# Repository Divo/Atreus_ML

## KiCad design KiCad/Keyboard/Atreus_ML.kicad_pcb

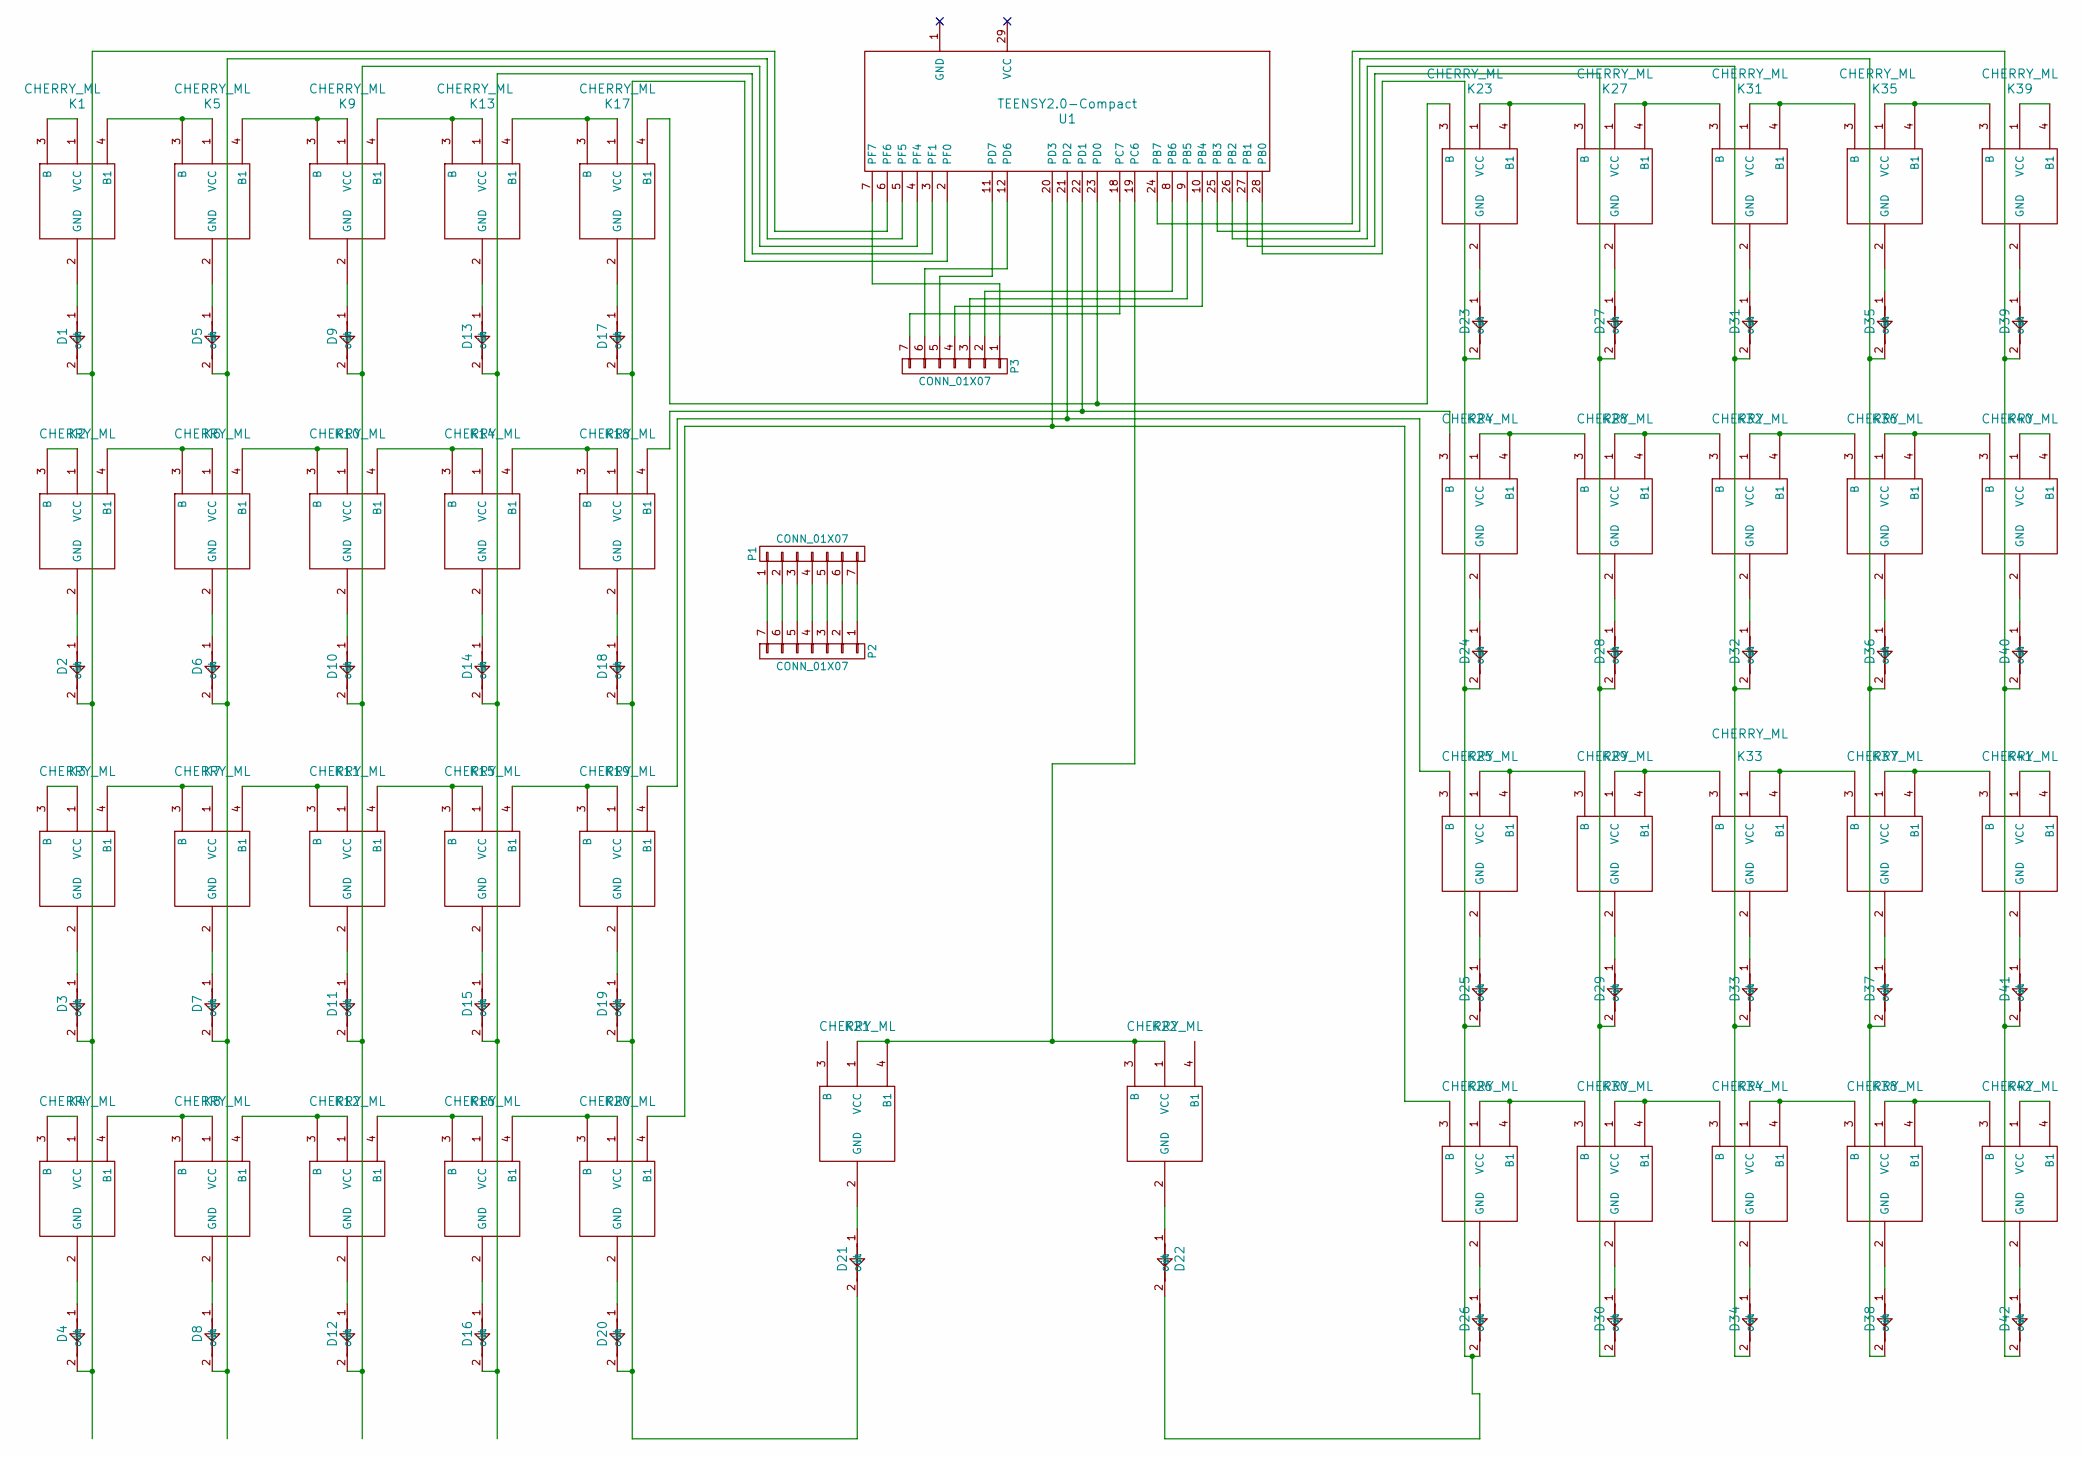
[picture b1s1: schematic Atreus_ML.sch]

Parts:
D1, D2, D3, D4, D5, D6, D7, D8, D9, D10, D11, D12, D13, D14, D15, D16, D17, D18, D19, D20, D21, D22, D23, D24, D25, D26, D27, D28, D29, D30, D31, D32, D33, D34, D35, D36, D37, D38, D39, D40, D41, D42: 4148; 4148_rev2
K1, K2, K3, K4, K5, K6, K7, K8, K9, K10, K11, K12, K13, K14, K15, K16, K17, K18, K19, K20, K21, K22, K23, K24, K25, K26, K27, K28, K29, K30, K31, K32, K33, K34, K35, K36, K37, K38, K39, K40, K41, K42: CHERRY_ML; CHERRY_ML_Etch
P1, P2, P3: CONN_01X07; Pin_Header_Straight_1x07
U1: TEENSY2.0-Compact; TEENSY_2.0-Compact

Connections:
unnamed: D1.1 (in), K1.2 (GND)
unnamed: D1.2 (out), D2.2 (out), D3.2 (out), D4.2 (out), U1.6 (PF6)
unnamed: D2.1 (in), K2.2 (GND)
unnamed: D3.1 (in), K3.2 (GND)
unnamed: D4.1 (in), K4.2 (GND)
unnamed: D5.1 (in), K5.2 (GND)
unnamed: D5.2 (out), D6.2 (out), D7.2 (out), D8.2 (out), U1.5 (PF5)
unnamed: D6.1 (in), K6.2 (GND)
unnamed: D7.1 (in), K7.2 (GND)
unnamed: D8.1 (in), K8.2 (GND)
unnamed: D9.1 (in), K9.2 (GND)
unnamed: D10.1 (in), K10.2 (GND)
unnamed: D9.2 (out), D10.2 (out), D11.2 (out), D12.2 (out), U1.4 (PF4)
unnamed: D11.1 (in), K11.2 (GND)
unnamed: D12.1 (in), K12.2 (GND)
unnamed: D13.1 (in), K13.2 (GND)
unnamed: D13.2 (out), D14.2 (out), D15.2 (out), D16.2 (out), U1.3 (PF1)
unnamed: D14.1 (in), K14.2 (GND)
unnamed: D15.1 (in), K15.2 (GND)
unnamed: D16.1 (in), K16.2 (GND)
unnamed: D17.1 (in), K17.2 (GND)
unnamed: D17.2 (out), D18.2 (out), D19.2 (out), D20.2 (out), D21.2 (out), U1.2 (PF0)
unnamed: D18.1 (in), K18.2 (GND)
unnamed: D19.1 (in), K19.2 (GND)
unnamed: D20.1 (in), K20.2 (GND)
unnamed: D21.1 (in), K21.2 (GND)
unnamed: D22.1 (in), K22.2 (GND)
unnamed: D22.2 (out), D23.2 (out), D24.2 (out), D25.2 (out), D26.2 (out), U1.28 (PB0)
unnamed: D23.1 (in), K23.2 (GND)
unnamed: D24.1 (in), K24.2 (GND)
unnamed: D25.1 (in), K25.2 (GND)
unnamed: D26.1 (in), K26.2 (GND)
unnamed: D27.1 (in), K27.2 (GND)
unnamed: D27.2 (out), D28.2 (out), D29.2 (out), D30.2 (out), U1.27 (PB1)
unnamed: D28.1 (in), K28.2 (GND)
unnamed: D29.1 (in), K29.2 (GND)
unnamed: D30.1 (in), K30.2 (GND)
unnamed: D31.1 (in), K31.2 (GND)
unnamed: D31.2 (out), D32.2 (out), D33.2 (out), D34.2 (out), U1.26 (PB2)
unnamed: D32.1 (in), K32.2 (GND)
unnamed: D33.1 (in), K33.2 (GND)
unnamed: D34.1 (in), K34.2 (GND)
unnamed: D35.1 (in), K35.2 (GND)
unnamed: D35.2 (out), D36.2 (out), D37.2 (out), D38.2 (out), U1.25 (PB3)
unnamed: D36.1 (in), K36.2 (GND)
unnamed: D37.1 (in), K37.2 (GND)
unnamed: D38.1 (in), K38.2 (GND)
unnamed: D39.1 (in), K39.2 (GND)
unnamed: D39.2 (out), D40.2 (out), D41.2 (out), D42.2 (out), U1.24 (PB7)
unnamed: D40.1 (in), K40.2 (GND)
unnamed: D41.1 (in), K41.2 (GND)
unnamed: D42.1 (in), K42.2 (GND)
unnamed: K1.1 (VCC), K1.3 (B)
unnamed: K1.4 (B1), K5.1 (VCC), K5.3 (B)
unnamed: K2.1 (VCC), K2.3 (B)
unnamed: K2.4 (B1), K6.1 (VCC), K6.3 (B)
unnamed: K3.1 (VCC), K3.3 (B)
unnamed: K3.4 (B1), K7.1 (VCC), K7.3 (B)
unnamed: K4.1 (VCC), K4.3 (B)
unnamed: K4.4 (B1), K8.1 (VCC), K8.3 (B)
unnamed: K5.4 (B1), K9.1 (VCC), K9.3 (B)
unnamed: K6.4 (B1), K10.1 (VCC), K10.3 (B)
unnamed: K10.4 (B1), K14.1 (VCC), K14.3 (B)
unnamed: K7.4 (B1), K11.1 (VCC), K11.3 (B)
unnamed: K11.4 (B1), K15.1 (VCC), K15.3 (B)
unnamed: K8.4 (B1), K12.1 (VCC), K12.3 (B)
unnamed: K12.4 (B1), K16.1 (VCC), K16.3 (B)
unnamed: K9.4 (B1), K13.1 (VCC), K13.3 (B)
unnamed: K13.4 (B1), K17.1 (VCC), K17.3 (B)
unnamed: K14.4 (B1), K18.1 (VCC), K18.3 (B)
unnamed: K15.4 (B1), K19.1 (VCC), K19.3 (B)
unnamed: K16.4 (B1), K20.1 (VCC), K20.3 (B)
unnamed: K17.4 (B1), K23.3 (B), U1.23 (PD0)
unnamed: K18.4 (B1), K24.3 (B), U1.22 (PD1)
unnamed: K19.4 (B1), K25.3 (B), U1.21 (PD2)
unnamed: K20.4 (B1), K26.3 (B), U1.20 (PD3)
unnamed: K21.1 (VCC), K21.4 (B1), K22.1 (VCC), K22.3 (B), U1.19 (PC6)
unnamed: K23.1 (VCC), K23.4 (B1), K27.3 (B)
unnamed: K24.1 (VCC), K24.4 (B1), K28.3 (B)
unnamed: K25.1 (VCC), K25.4 (B1), K29.3 (B)
unnamed: K26.1 (VCC), K26.4 (B1), K30.3 (B)
unnamed: K27.1 (VCC), K27.4 (B1), K31.3 (B)
unnamed: K28.1 (VCC), K28.4 (B1), K32.3 (B)
unnamed: K29.1 (VCC), K29.4 (B1), K33.3 (B)
unnamed: K30.1 (VCC), K30.4 (B1), K34.3 (B)
unnamed: K31.1 (VCC), K31.4 (B1), K35.3 (B)
unnamed: K32.1 (VCC), K32.4 (B1), K36.3 (B)
unnamed: K33.1 (VCC), K33.4 (B1), K37.3 (B)
unnamed: K34.1 (VCC), K34.4 (B1), K38.3 (B)
unnamed: K35.1 (VCC), K35.4 (B1), K39.3 (B)
unnamed: K36.1 (VCC), K36.4 (B1), K40.3 (B)
unnamed: K37.1 (VCC), K37.4 (B1), K41.3 (B)
unnamed: K38.1 (VCC), K38.4 (B1), K42.3 (B)
unnamed: K39.1 (VCC), K39.4 (B1)
unnamed: K40.1 (VCC), K40.4 (B1)
unnamed: K41.1 (VCC), K41.4 (B1)
unnamed: K42.1 (VCC), K42.4 (B1)
unnamed: P1.1, P2.7
unnamed: P1.2, P2.6
unnamed: P1.3, P2.5
unnamed: P1.4, P2.4
unnamed: P1.5, P2.3
unnamed: P1.6, P2.2
unnamed: P1.7, P2.1
unnamed: P3.1, U1.7 (PF7)
unnamed: P3.2, U1.8 (PB6)
unnamed: P3.3, U1.9 (PB5)
unnamed: P3.4, U1.10 (PB4)
unnamed: P3.5, U1.11 (PD7)
unnamed: P3.6, U1.12 (PD6)
unnamed: P3.7, U1.18 (PC7)

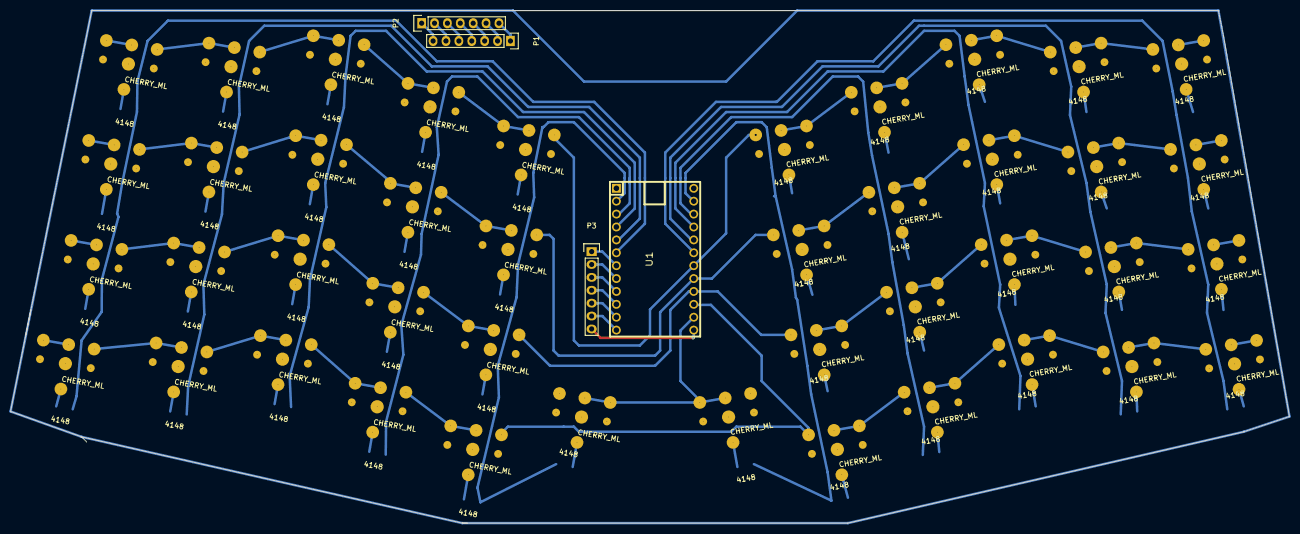
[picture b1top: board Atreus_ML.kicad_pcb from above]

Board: 2 copper layers, 252.0 x 101.0 mm, 88 parts (0 on the bottom side), 111 nets.

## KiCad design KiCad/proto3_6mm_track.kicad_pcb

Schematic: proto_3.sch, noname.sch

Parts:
D1, D2, D3, D4: 4148
K1, K2, K3, K4: CHERRY_ML
P1: CONN_4

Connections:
unnamed: D3.1 (in), K3.2 (GND)
unnamed: D2.1 (in), K2.2 (GND)
unnamed: D4.1 (in), K4.2 (GND)
unnamed: D1.2 (out), D2.2 (out), P1.3
unnamed: D3.2 (out), D4.2 (out), P1.4
unnamed: D1.1 (in), K1.2 (GND)
unnamed: K1.4 (B1), K3.1 (VCC), K3.3 (B)
unnamed: K2.1 (VCC), K2.3 (B), P1.1
unnamed: K2.4 (B1), K4.1 (VCC), K4.3 (B)
unnamed: K1.1 (VCC), K1.3 (B), P1.2

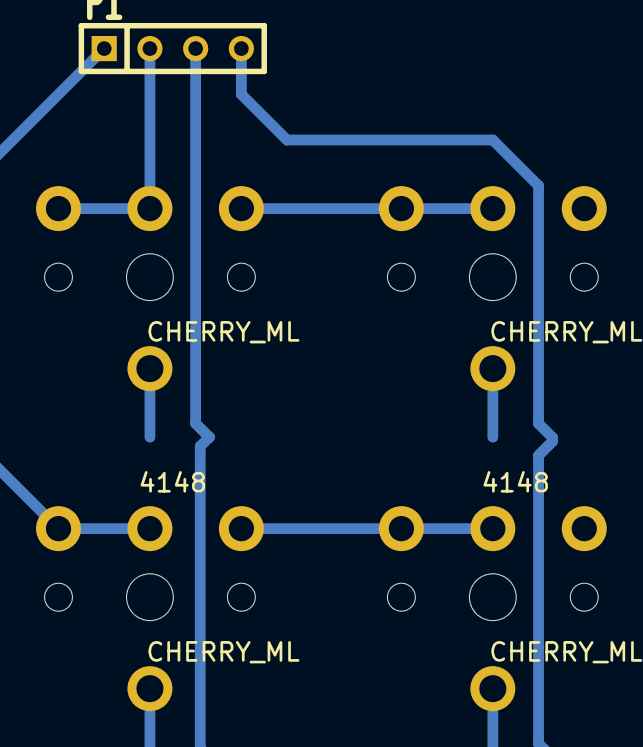
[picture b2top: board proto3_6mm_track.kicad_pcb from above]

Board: 2 copper layers, 9 parts (0 on the bottom side), 10 nets.

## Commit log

2015-11-08 :neckbeard: Added .gitattributes & .gitignore files
2015-11-08 Inital import
    Inital import, something wrong with diodes not connecting properly. Try
    making both schematic and footprint from scratch?
2015-11-09 working test schematic
2015-11-09 last update on proto 2 for tonight, saved this time
2015-11-21 Third prototype
2015-11-21 proto3 with .6mm wide tracks
2015-11-25 register key press with arduino uno
2016-02-21 Single button code example
2016-02-21 Adding single button example sketch
2016-02-29 Got rough prototype keyboard firmware up and running. Who am I kidding, this will be the most refined it ever gets
2016-03-07 Organizing + starting on main design
2016-03-08 First draft of schematic digram
2016-03-21 Redoing lost work: Removing stopid modifier keys as single row
2016-03-27 Netlist
2016-03-28 Fixed logical layout, starting physical
2016-03-28 Switching to teensu compact
2016-03-28 Basic Layout done
2016-03-28 Rotation done
2016-03-28 Layout done!
2016-03-28 Rev one is done!
2016-03-28 Last cleanup
2016-03-29 Starting rev 2, cleaning up columns
2016-03-29 Rev 2 is done
2016-03-29 Adding gerber + drill files
2016-03-30 Small change to a trace and gerber files
2016-03-30 Drill files
2016-03-30 SHit attempt at edge cuts
2016-03-30 Removing old gerbers
2016-03-30 Revert "Removing old gerbers"
    This reverts commit 3084752967e5eed63478fe47835f68dc672781bc.
2016-03-30 Revert "SHit attempt at edge cuts"
    This reverts commit ffdaeb101ec3ff8e95e5d2729ed6d2ed464c68dc.
2016-03-30 Edge cuts, they seem ok
2016-03-30 Plot of rev 2
2016-03-30 Files for rev 2
2016-03-30 Rev 2 pdf for printing
2016-03-31 Rev 3, now with headers for unused pins
2016-03-31 Rev 4
2016-03-31 Rev 4 phase 2?
2016-03-31 Final design for etching
2016-04-07 Half a fix for design and some test code
2016-04-08 Fixing design whoopsie
2016-04-11 Sometgine resembling a test firmware
2016-04-16 Adding simple layer
2016-04-16 =initial firmware, know come the layers
2016-04-17 Trying to get modifiers to work. Code works without modifier sends
2016-04-17 Layers work, modifier still do not
2016-04-18 Will probably switch to tmk now, teensy lib causing too much pain
2016-04-23 Something of a solution for modified key issues
2016-04-23 durip
2016-04-24 Shift stuff is done
2016-05-03 swapping space and backspace
2016-05-03 have space and backspace the same on all layers
2016-05-03 Moving arrows to wasd
2016-05-04 reworking layout a bit again
2016-05-04 removing some prints and rework release logic for updated keymap
2016-05-04 working on modifier key logic
2016-05-04 still sending duplicate presses
2016-05-04 still need to sort the release events
2016-05-10 rejigging layout and led on layer 1
